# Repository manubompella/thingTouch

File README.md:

# thingTouch
This repo contains experiments with touch buttons and sliders

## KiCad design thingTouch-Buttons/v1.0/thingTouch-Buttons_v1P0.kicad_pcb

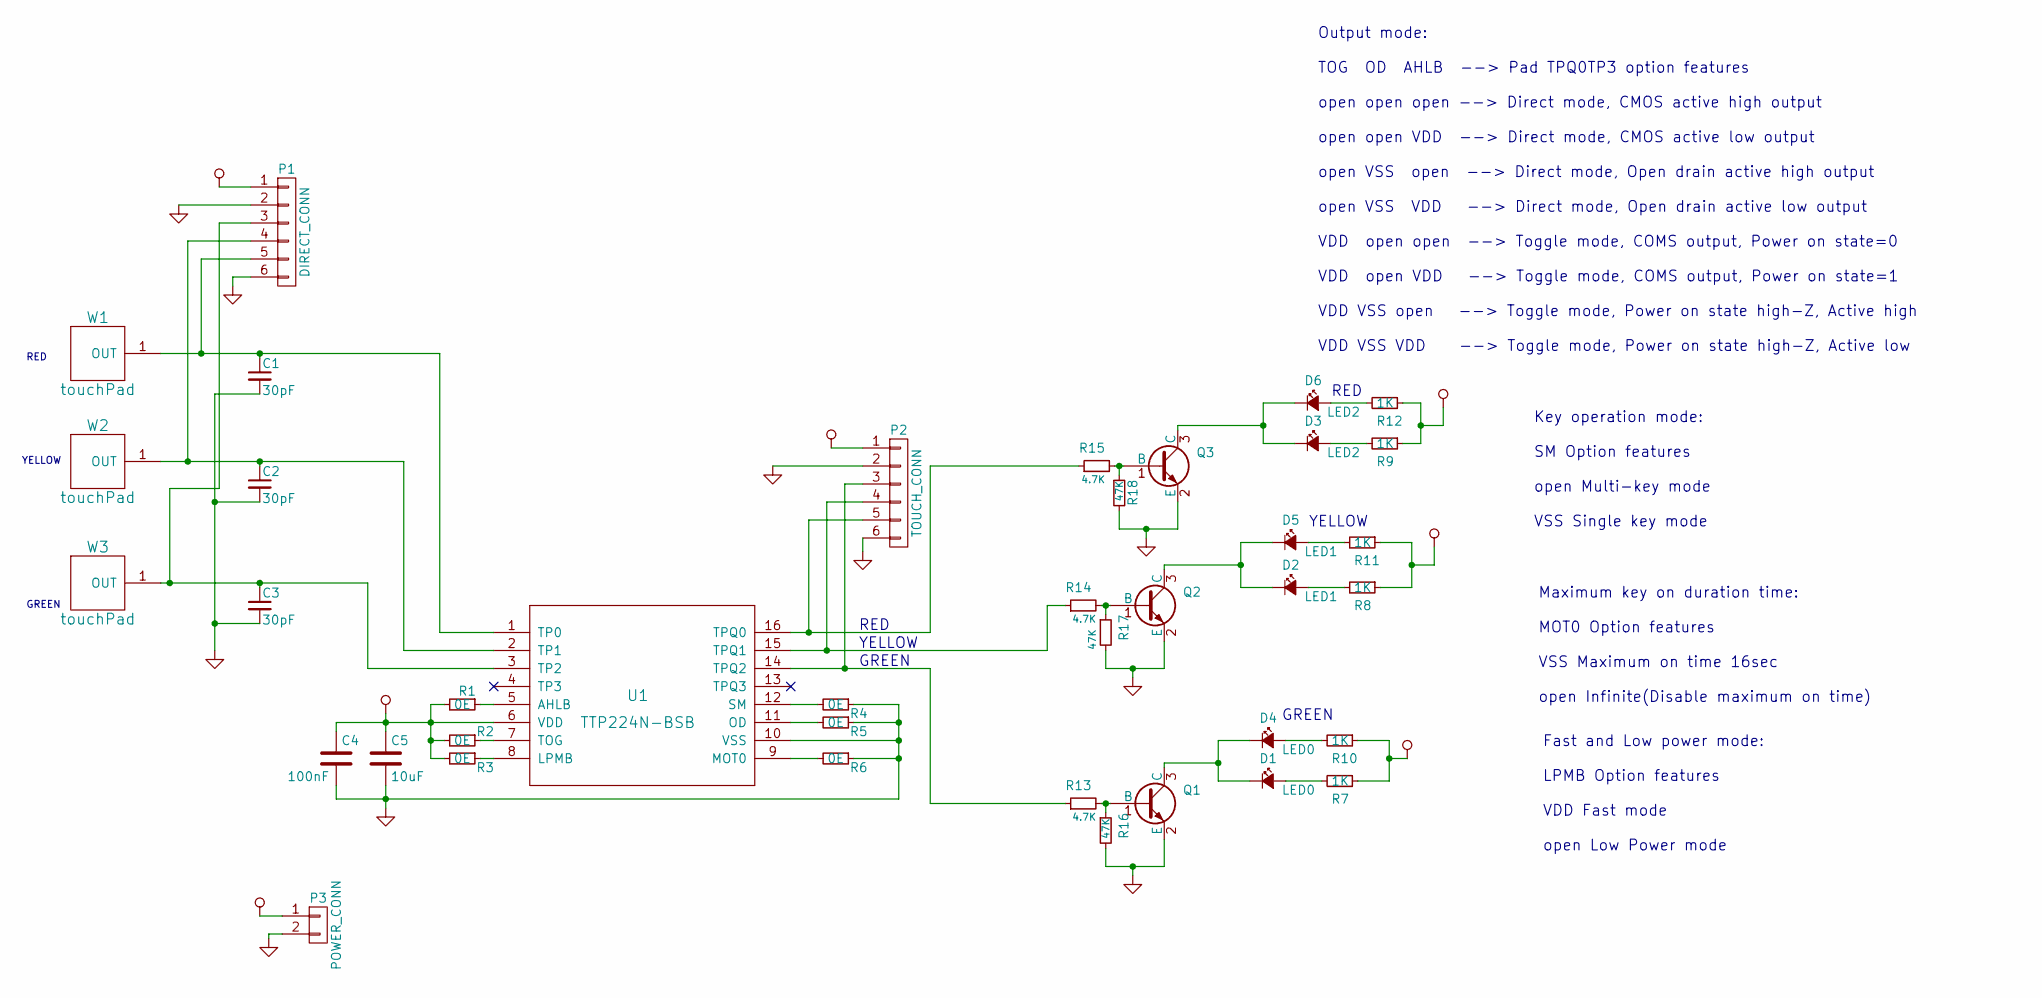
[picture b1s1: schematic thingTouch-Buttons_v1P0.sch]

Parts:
C1, C2, C3: 30pF; C_0805_HandSoldering
C4: 100nF; C_0805_HandSoldering
C5: 10uF; C_0805_HandSoldering
D1, D4: LED0; LED_0805_Side_led
D2, D5: LED1; LED_0805_Side_led
D3, D6: LED2; LED_0805_Side_led
P1: DIRECT_CONN; JST_EH_S06B-EH_06x2.50mm_Angled
P2: TOUCH_CONN; JST_EH_S06B-EH_06x2.50mm_Angled
P3: POWER_CONN; JST_EH_S02B-EH_02x2.50mm_Angled
Q1, Q2, Q3: MMBT3904; SOT-23
R1, R2, R3, R4, R5, R6: 0E; R_0805_HandSoldering
R7, R8, R9, R10, R11, R12: 1K; R_0805_HandSoldering
R13, R14, R15: 4.7K; R_0805_HandSoldering
R16, R17, R18: 47K; R_0805_HandSoldering
U1: TTP224N-BSB; SSOP-16_3.9x4.9mm_Pitch0.635mm
W1, W2, W3: touchPad; TouchPad-round-1000

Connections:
GND: C1.2, C2.2, C3.2, C4.2, C5.2, P1.2, P1.6, P2.2, P2.6, P3.2, Q1.2 (E), Q2.2 (E), Q3.2 (E), R4.1, R5.1, R6.1, R16.2, R17.2, R18.2, U1.10 (VSS)
unnamed: C1.1, P1.5, U1.1 (TP0), W1.1
unnamed: C2.1, P1.4, U1.2 (TP1), W2.1
unnamed: C3.1, P1.3, U1.3 (TP2), W3.1
unnamed: D1.1 (K), D4.1 (K), Q1.3 (C)
unnamed: D1.2 (A), R7.2
unnamed: D2.1 (K), D5.1 (K), Q2.3 (C)
unnamed: D2.2 (A), R8.2
unnamed: D3.1 (K), D6.1 (K), Q3.3 (C)
unnamed: D3.2 (A), R9.2
unnamed: D4.2 (A), R10.2
unnamed: D5.2 (A), R11.2
unnamed: D6.2 (A), R12.2
unnamed: P2.3, R13.1, U1.14 (TPQ2)
unnamed: P2.4, R14.1, U1.15 (TPQ1)
unnamed: P2.5, R15.1, U1.16 (TPQ0)
unnamed: Q1.1 (B), R13.2, R16.1
unnamed: Q2.1 (B), R14.2, R17.1
unnamed: Q3.1 (B), R15.2, R18.1
unnamed: R1.1, U1.5 (AHLB)
unnamed: R2.1, U1.7 (TOG)
unnamed: R3.1, U1.8 (LPMB)
unnamed: R4.2, U1.12 (SM)
unnamed: R5.2, U1.11 (OD)
unnamed: R6.2, U1.9 (MOT0)
VDD: C4.1, C5.1, P1.1, P2.1, P3.1, R1.2, R2.2, R3.2, R7.1, R8.1, R9.1, R10.1, R11.1, R12.1, U1.6 (VDD)

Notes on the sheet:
Output mode: TOG OD AHLB --> Pad TPQ0TP3 option features open open open --> Direct mode, CMOS active high output open open VDD --> Direct mode, CMOS active low output open VSS open --> Direct mode, Open drain active high output open VSS VDD --> Direct mode, Open drain active low output VDD open ope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
Key operation mode: SM Option features open Multi-key mode VSS Single key mode
Maximum key on duration time: MOT0 Option features VSS Maximum on time 16sec open Infinite(Disable maximum on time)
Fast and Low power mode: LPMB Option features VDD Fast mode open Low Power mode
RED
GREEN
YELLOW

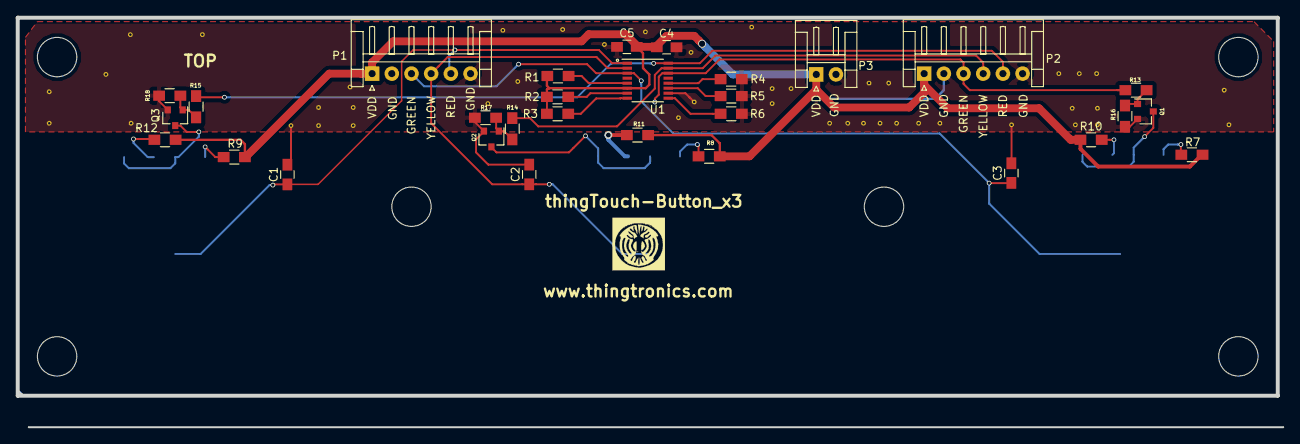
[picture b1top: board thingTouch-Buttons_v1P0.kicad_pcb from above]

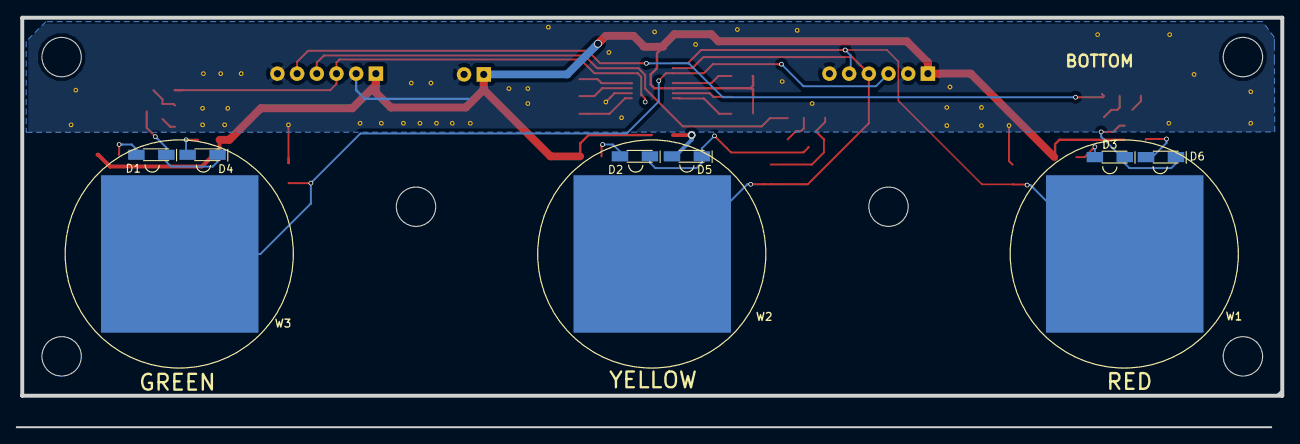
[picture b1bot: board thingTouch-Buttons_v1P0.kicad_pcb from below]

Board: 2 copper layers, 160.7 x 52.0 mm, 39 parts (9 on the bottom side), 26 nets.

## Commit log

2017-07-17 initial commit; getting ready the directory
2017-07-17 intermediate commit
2017-07-17 schematic complete with 3 buttons
2017-07-17 netlist generated
2017-07-17 basic routing done
2017-07-18 final routing done; verification left
2017-07-18 following changes are done
    Layout following changes done
    -> 2.0mm mounting holes added
    -> company logo and name
    -> fab details
    -> rerouting of touch signals and VDD signals
    -> Bom created
2017-07-18 verified the layout
2017-07-26 in schematic transistor switching,side leds added right angle connector s added
    in schematic transistor switching logic, side leds added ,right angle
    connector s added
2017-07-31 merged pull request
2017-08-01 Gerbers generated, design verified
    Gerbers generated, design verified
